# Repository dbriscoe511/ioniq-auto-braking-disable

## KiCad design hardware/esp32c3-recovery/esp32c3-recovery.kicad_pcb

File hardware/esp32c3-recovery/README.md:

# ESP32-C3 add-on: Parking Safety auto-disable

KiCad 10 schematic and PCB for the add-on board that taps the console switch panel
(CON1 of PCB IP-678A, see [../../docs/electronics.md](../../docs/electronics.md))
and presses the Parking Safety button at startup based on CAN status.

PDF: [out/esp32c3-recovery.pdf](out/esp32c3-recovery.pdf)

## Files

| File | What |
|---|---|
| `esp32c3-recovery.kicad_pro` / `.kicad_sch` | KiCad project and the single sheet |
| `esp32c3_recovery.kicad_sym` + `sym-lib-table` | Project symbol library (empty: every symbol is stock KiCad) |
| `tools/gen.py` | Generates the sheet and project library; **edit this, not the sheet** |
| `tools/check.sh` | Regenerate, ERC, netlist check against intended nets, library check, PDF/SVG/PNG export |
| `esp32c3-recovery.kicad_pcb` | The routed board (generated; **edit `tools/gen_pcb.py`**) |
| `esp32c3_recovery.pretty/` + `fp-lib-table` | Project footprints from `tools/footprints.py`: WROOM-02 (stock minus its 0.2 mm vias), WAGO 2060, TS-1187A switch |
| `esp32c3_recovery.3dshapes/` | 3D models for the WAGO, the switch and F1 (sources below) |
| `tools/gen_pcb.py` | Placement (`PLACE`), keep-outs, ground pours, stitching vias, JLC BOM/CPL |
| `tools/pcb.sh` | Full PCB build: schematic checks, place, Freerouting, pours, DRC, JLC outputs |
| `out/jlc/` | Upload set: `*-gerbers.zip`, `*-bom.csv`, `*-cpl.csv` |

Everything else uses stock KiCad symbols and footprints. Each JLC-assembled
part carries `Footprint` and `LCSC` fields.

## PCB

Sized for a **Hammond 1551K** box (1551KBK black, 1551KTBU translucent blue;
80 x 40 x 20 mm ABS). The outline is Hammond's maximum board size (74 x 34 mm,
with 6.25 mm notches at the top-right and bottom-left corners for the lid-screw
posts), shrunk by 0.25 mm on every side: 73.5 x 33.5 mm. Corners are rounded
R1, and the two inside notch corners R3 (Hammond's radius). 2 layers, 1.6 mm,
every part JLC-placed on the top side (Economic PCBA), including the ESP32-C3
module: nothing to hand-solder. DRC is clean (0 violations, 0 unconnected,
schematic parity OK).

- **Mounting: four 2.5 mm non-plated holes on a 40 x 28.5 mm rectangle.**
  - **H1 (top left) and H2 (bottom right) sit on the box's two PCB bosses.**
    Hammond puts them 17 mm from the left edge and 2.75 mm from the top of
    its maximum board, which is board (16.75, 2.5) here. Use Hammond's
    #2 x 3/16" self-tapping PCB screws (1551ATS100).
  - **H3 (top right) and H4 (bottom left)** complete the rectangle for bench
    standoffs; nothing sits under them in the box. 2.5 mm is tight for M2.5,
    so use M2 screws or standoffs there.
  - No top-layer tracks or vias within 2.7 mm of H1/H2, so the box screws'
    heads sit only on the ground pour. The board sits
  4 mm off the floor and the tallest part (the WAGOs, 4.5 mm) clears the lid by
  about 5.9 mm.
- **U2 is an ESP32-C3-WROOM-02-N4** (C2934560, 18 x 20 mm, 4 MB flash, PCB
  antenna, -40 to 85 C), placed by JLC. It lies on its side with the antenna
  end at the left edge, so Espressif's keep-out (5 mm round the antenna, in
  KiCad's footprint) covers the left 6.3 mm of the board and runs off the
  edge. Pins 10-18 (IO10..IO0) run along the top, 1-9 (3V3, EN, IO4..IO9,
  GND) along the bottom.
  - The project footprint is KiCad's stock one without its twelve 0.2 mm
    vias in the ground pad (JLC's standard minimum drill is 0.3 mm); five
    0.3 mm vias take their place.
  - No top-layer tracks under the module inside its pad rows.
  - The nearest screw to the antenna is H1's, about 10 mm from the antenna
    end.
- **3.3 V:** U4 AMS1117-3.3 from +5V (about 0.1 W), C7 22u at its output and
  C8 100n at the module's 3V3 pin. The L78M05 still makes 5V_REG for the
  TJA1051.
- **Reset, boot, strapping:** R8 10k + C9 1u on EN (power-on delay), SW2
  RESET and SW1 BOOT (TS-1187A, JLC basic), and 10k pull-ups on GPIO9, GPIO8
  and GPIO2. For the ROM bootloader, hold BOOT and tap RESET.
- **USB and debug pads:** J6 USB-C (HRO TYPE-C-31-M-12, C165948) with 5.1k
  CC pull-downs R12/R13, fitted by JLC, on the module's native USB
  (GPIO18/19). The cable plugs in from the board's bottom edge, which faces a
  long wall in the box. Next to it are bare test pads:
  - TP1 5V (VBUS), TP2 D-, TP3 D+, TP4 GND: the same native USB, for a
    pogo-pin or tack-soldered cable;
  - TP5 TX, TP6 RX: UART0, where the firmware logs.
  - VBUS reaches +5V through D4, so USB alone runs the board (the TJA1051
    stays off the bus without 12 V). The labels are on the bottom silkscreen.
- **J1-J5 are WAGO 2060-451/998-404 push-in terminals**, one per wire, wire
  entry facing the right end wall. From the top: VBAT, CANH, CANL, BTN, GND,
  printed at each entry on the top and under each terminal on the bottom.
  - The entry faces sit about 7.5 mm in from the board edge, about 8.3 mm
    from the box's inner wall. J1 and J5 are 8 mm either side of centre, so
    wires from one central hole can't enter them straight on. Either thread
    the harness through the end-wall hole, wire the board outside the box,
    then lower it in, or cut a U-slot down from the rim of the right end wall.
    The hole centre should be about 9.5 mm above the outside bottom (a guess
    from the 3D model). Thin wire (22-24 AWG) makes the fan-out easier.
  - GND is the terminal next to H2's screw.
  - Wire: 0.2-0.75 mm2 (24-18 AWG) solid, or stranded with the release button
    pressed, stripped 7-9 mm. Ferrules only for 0.25-0.34 mm2. Don't tin
    stranded wire.
  - The footprint follows WAGO's land pattern (data sheet 11.02.2026): 14 mm
    overall, a 6 mm pad under the conductor entry, a 3.5 mm pad at the back,
    and 2.0 mm wide (the 1.2 mm contact tail plus 0.4 mm each side).
  - Each terminal is held by its two solder pads only. Tie the harness down
    to the box (a cable tie through the grommet), and optionally put a bead of
    RTV across the five bodies after wiring.
- **D3, user LED:** red 0603 LED on GPIO1 (active high, ~1.3 mA through R7
  1k), at the top-left corner, board (8.0, 1.9) from the top-left corner. The
  box is opaque, so drill a ~2 mm hole in the lid above it. The translucent
  1551KTBU may also work, but blue plastic dims red light.
- **Regulator heat:** the DPAK tab connects solid to the top ground pour, with
  9 vias in the tab plus a ring beside it into the bottom pour.
- **Rules:** power nets (VBAT, 5V_REG, +5V, +3V3) use 0.5 mm tracks, other nets
  0.25 mm. GND is routed at 0.25 mm too; the pours on both layers carry
  its current. Clearance is 0.2 mm, vias 0.6/0.3 mm, copper-to-edge 0.3 mm or more.

**3D models** (`esp32c3_recovery.3dshapes/`, used unmodified; the footprints set the offset and rotation):
- `WAGO_2060-451_998-404.step`: the EasyEDA/LCSC model for C2765054, fetched
  with `easyeda2kicad --3d --lcsc_id=C2765054`.
- `Fuse_1812_4532Metric.step`: the EasyEDA/LCSC model for C70113 (F1), fetched
  the same way. KiCad ships none for that footprint; `MODEL_OVERRIDE` in
  `tools/gen_pcb.py` swaps it in.
- `SW_TS-1187A.step`: the EasyEDA/LCSC model for C318884 (SW1, SW2), with
  its footprint pads taken from JLC's footprint.
- All other parts, including the WROOM-02, use KiCad's stock models.

**Rebuild:** `JAVA=<java 25+> FREEROUTING=<freerouting-2.x.jar> tools/pcb.sh`.
`pcb.sh` re-runs Freerouting while its result changes. If a change leaves
unconnected pads, adjust `PLACE`; check two-terminal parts' pad 1 orientation
first.

### Before ordering

- **Check the fit against a real 1551K** if one is on hand: the hole positions
  and the corner notches come from Hammond's drawing (REV 31.08.2023), not a
  measured box.
- **Tick "Confirm Parts Placement" when ordering**, and check every part in
  JLC's placement preview: the polarity of U3 (pin 1), Q1, U1, D1, D2, D3 and
  D4, and the WAGO orientation, with the wire entry (6 mm pad) facing the
  right edge.
  - **New since the last preview check:** U2 (the module: antenna end at the
    left edge, pin 1 bottom-left), U4 (SOT-223, tab toward the top edge) and
    SW1/SW2. JLCKicadTools has no entry for the WROOM-02; the CPL uses
    KiCad's rotation, so correct it in the preview if JLC's model is turned.
  - The CPL adds SOIC +270, SOT-23 +180 and SOT-223 +180. The SOT-23 value
    comes from JLC's own preview on 2026-11-17, which showed Q1 90 degrees off
    with the JLCKicadTools -90. That preview also showed U1, D1, D2, D3, F1,
    U3 and the WAGOs correct.
- **WAGO position:** JLC's own footprint for C2765054 has its origin 0.57 mm
  toward the back pad from ours. The CPL reports that point, so JLC's part
  lands centred on our pads. If the preview still shows the terminals shifted
  along their length, correct it there.
- **Economic assembly:** JLC's part pages list "Economic and Standard" for
  the module C2934560, the WAGO C2765054, F1 C70113, U3 C38695, U4 C6186
  and D1 C19077573 (checked 2026-11-17). Order five WAGOs per board.
- Gerbers, drill files and the CPL share the bounding box's lower-left corner
  as origin.

## BOM (JLCPCB assembly)

Every part is placed by JLC (J6's shell pegs are through-hole, soldered in the
same pass); the test pads are bare copper. Part status was checked
against JLC's parts API on 2026-11-16/17.
Basic and preferred parts carry no feeder fee on Economic PCBA. Each plain
extended part type adds about $3 per order.

| Ref | Part | Package | LCSC | JLC status |
|---|---|---|---|---|
| R1, R7 | 1k | 0603 | C21190 | basic |
| R2, R8, R9, R10, R11 | 10k | 0603 | C25804 | basic |
| R3 | 200 | 0805 | C17540 | basic |
| R4 | 100k | 0603 | C25803 | basic |
| R5 | 27k | 0603 | C22967 | basic |
| R6 | 4.7k | 0603 | C23162 | basic |
| C1 | 1u 50V X7R | 0805 | C28323 | basic |
| C2, C4, C5, C6, C8 | 100n 50V X7R | 0603 | C14663 | basic |
| C3, C7 | 22u 25V X5R | 0805 | C45783 | basic |
| C9 | 1u 50V X5R | 0603 | C15849 | basic |
| U4 | AMS1117-3.3 | SOT-223 | C6186 | basic |
| SW1, SW2 | TS-1187A-B-A-B tactile switch | 5.1 x 5.1 mm SMD | C318884 | basic |
| U1 | L78M05ABDT-TR | DPAK | C58069 | basic |
| D2, D4 | B5819W | SOD-123 | C8598 | basic |
| Q1 | MMBT3904 | SOT-23 | C20526 | basic |
| D1 | SMBJ18A | SMB | C19077573 | preferred (no basic TVS exists) |
| U3 | TJA1051T/3/1J | SOIC-8 | C38695 | extended (no basic CAN transceiver exists) |
| F1 | mSMD050-60V | 1812 | C70113 | extended (no basic or preferred PTC exists) |
| J1-J5 | WAGO 2060-451/998-404 (x5) | SMD terminal | C2765054 | extended (one part type, one fee) |
| D3 | KT-0603R red LED | 0603 | C2286 | basic |
| U2 | ESP32-C3-WROOM-02-N4 | 18 x 20 mm module | C2934560 | extended |
| J6 | USB-C, HRO TYPE-C-31-M-12 | SMD + THT shell | C165948 | extended |
| R12, R13 | 5.1k | 0603 | C23186 | basic |

Five extended part types (U2, U3, F1, J1-J5, J6): about $15 in feeder fees per
order.

**CAN transceiver.** JLC has no basic CAN transceiver. Two are preferred
(fee-free). TJA1050T (C6952) needs 5 V, outputs 5 V on RXD and has no silent
pin, so it doesn't fit. SN65HVD230DR (C12084) runs on 3.3 V, and its RS-high
standby mode is a true listen-only mode (driver off, receiver unchanged), so it
would work with the same firmware. It is not used here because its bus pins
are rated only -4 to +16 V absolute maximum and it is rated to 85 C. The
TJA1051T/3 is the chip on the Adafruit CAN Pal. It is AEC-Q100, with -58 to
+58 V bus pins and the same S (silent) pin, for about $0.55 plus one
extended-part fee.

## Pin map (ESP32-C3-WROOM-02)

| GPIO | Use |
|---|---|
| GPIO3 (ADC) | Press sense: BTN through 100k/27k divider, ~1 V threshold |
| GPIO5 | TJA1051 S (silent). R6 4.7k pull-up keeps the transceiver silent; firmware drives it high by default |
| GPIO6 | TJA1051 TXD (transmit possible, but off by default) |
| GPIO7 | TJA1051 RXD |
| GPIO10 | Button press drive on CON1-5 (1k to MMBT3904 base, 10k base pull-down) |
| GPIO1 | D3 user LED (active high, R7 1k) |
| GPIO2/8/9 | Strapping pins: 10k pull-ups; SW1 BOOT pulls GPIO9 low |
| GPIO18/19 | Native USB D-/D+ (J6, TP2/TP3) |
| GPIO20/21 | UART0 RX/TX (TP6/TP5), firmware log |
| EN | 10k/1u reset delay, SW2 RESET |

## Assumptions to verify before building

- **BTN line = CON1 pin 5.** The Parking Safety switch is hardwired there
  (~200 ohms in series, other side to ground; not read by the panel MCU) and
  pin 5 idles at 12.2 V in the car. See docs/findings.md. Measured in the car
  with the firmware running: GPIO3 reads ~2.5 V released (BTN ~11.8 V) and
  ~0.1 V with Q1 on (BTN ~0.5 V), so R3 = 200 ohms (mirroring the factory switch
  path) carries at most ~2.4 mA.
- **R3 is now 0805 (125 mW), down from 1 W.** Against the panel's weak (~5k)
  pull-up it dissipates about 1 mW. The 1 W rating only covered a stiff 12 V
  source on BTN (0.7 W), which the in-car readings rule out. There is no basic
  1206 at 200 ohms (C18002, 0.25 W, is extended).
- **Regulator:** L78M05 in DPAK (35 V max in, above the SMBJ18A's 29.2 V
  clamp). It has no reverse-battery protection, but the tap is behind the
  panel's D1/D2. At 14.4 V in and ~80 mA average (more in Wi-Fi bursts) it
  dissipates ~0.75 W, so give the DPAK tab a copper pour of a few cm^2.
- **Transceiver supply:** TJA1051 VCC (4.5-5.5 V) is fed from `5V_REG`
  before D2, because the Schottky drop on `+5V` can fall below 4.5 V. On USB
  power alone the transceiver sees VCC under-voltage and disengages from the
  bus (zero load), so there is no CAN receive on the bench without 12 V.
  VIO is the board's 3.3 V (U4), so RXD is 3.3 V logic.
- **No CAN termination** on this board: the tap sits mid-bus.
- **Parts added after the design review:** F1 PTC fuse, which limits fault
  current if the TVS fails short. D2 Schottky, which stops USB 5 V from
  back-feeding the regulator; D4 does the same the other way, so the 12 V
  supply can't push current into a USB host.

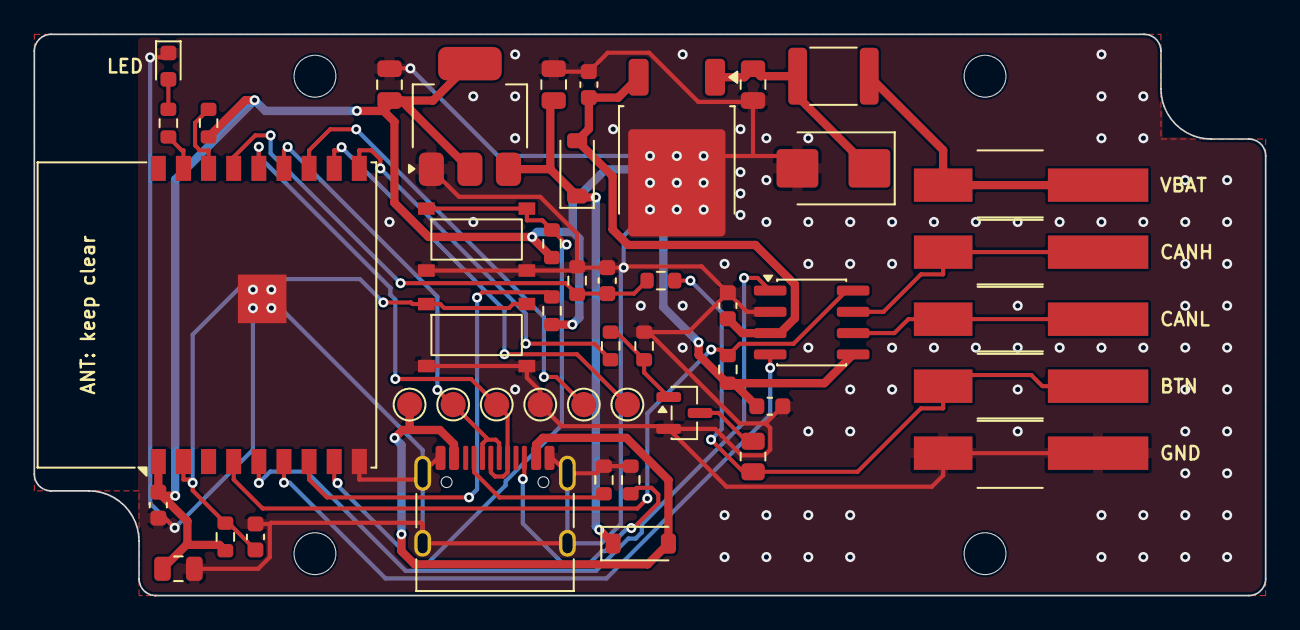
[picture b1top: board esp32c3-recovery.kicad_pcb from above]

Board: 2 copper layers, 73.5 x 33.5 mm, 51 parts (0 on the bottom side), 29 nets.

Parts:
C1: 1u 50V; C_0805_2012Metric
C2, C4, C5, C6, C8: 100n; C_0603_1608Metric
C3, C7, C10: 22u 25V; C_0805_2012Metric
C9: 1u; C_0603_1608Metric
D1: SMBJ18A; D_SMB
D2, D4: B5819W; D_SOD-123
D3: red; LED_0603_1608Metric
F1: 500mA 60V; Fuse_1812_4532Metric
H1, H2, H3, H4: #2; MountingHole_2.5mm
J1: VBAT; WAGO_2060-451_998-404
J2: CANH; WAGO_2060-451_998-404
J3: CANL; WAGO_2060-451_998-404
J4: BTN; WAGO_2060-451_998-404
J5: GND; WAGO_2060-451_998-404
J6: USB-C; USB_C_Receptacle_HRO_TYPE-C-31-M-12
Q1: MMBT3904; SOT-23
R1, R7: 1k; R_0603_1608Metric
R2, R8, R9, R10, R11: 10k; R_0603_1608Metric
R3: 200; R_0805_2012Metric
R4: 100k; R_0603_1608Metric
R5: 27k; R_0603_1608Metric
R6: 4.7k; R_0603_1608Metric
R12, R13: 5.1k; R_0603_1608Metric
SW1: BOOT; SW_TS-1187A
SW2: RESET; SW_TS-1187A
TP1: VBUS; TestPoint_Pad_D1.5mm
TP2: USB_DN; TestPoint_Pad_D1.5mm
TP3: USB_DP; TestPoint_Pad_D1.5mm
TP4: GND; TestPoint_Pad_D1.5mm
TP5: U0TXD; TestPoint_Pad_D1.5mm
TP6: U0RXD; TestPoint_Pad_D1.5mm
U1: L78M05; TO-252-2
U2: ESP32-C3-WROOM-02-N4; ESP32-C3-WROOM-02_JLC
U3: TJA1051T/3; SOIC-8_3.9x4.9mm_P1.27mm
U4: AMS1117-3.3; SOT-223-3_TabPin2

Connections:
+3V3: C6.1, C7.1, C8.1, C10.1, R6.1, R8.1, R9.1, R10.1, R11.1, U2.1, U3.5, U4.2
+5V: C3.1, D2.1, D4.1, U4.3
/5V_REG: C2.1, C5.1, D2.2, U1.3, U3.3
/BTN: J4.1, R3.1, R4.1
/BTN_DRIVE: R1.1, U2.10
/BTN_SENSE: C4.1, R4.2, R5.1, U2.15
/CANH: J2.1, U3.7
/CANL: J3.1, U3.6
/CAN_RX: U2.6, U3.4
/CAN_S: R6.2, U2.4, U3.8
/CAN_TX: U2.5, U3.1
/CC1: J6.A5, R12.1
/CC2: J6.B5, R13.1
/EN: C9.1, R8.2, SW2.1, U2.2
/IO2_STRAP: R11.2, U2.16
/IO8_STRAP: R10.2, U2.7
/IO9_BOOT: R9.2, SW1.1, U2.8
/LED: R7.1, U2.17
/U0RXD: TP6.1, U2.11
/U0TXD: TP5.1, U2.12
/USB_DN: J6.A7, J6.B7, TP2.1, U2.13
/USB_DP: J6.A6, J6.B6, TP3.1, U2.14
/VBAT_F: C1.1, D1.1, F1.2, U1.1
/VBUS: D4.2, J6.A4, J6.A9, J6.B4, J6.B9, TP1.1
GND: C1.2, C2.2, C3.2, C4.2, C5.2, C6.2, C7.2, C8.2, C9.2, C10.2, D1.2, D3.1, J5.1, J6.A1, J6.A12, J6.B1, J6.B12, J6.SH, Q1.2, R2.2, R5.2, R12.2, R13.2, SW1.2, SW2.2, TP4.1, U1.2, U2.9, U2.19, U3.2, U4.1
unnamed: D3.2, R7.2
unnamed: F1.1, J1.1
unnamed: Q1.1, R1.2, R2.1
unnamed: Q1.3, R3.2

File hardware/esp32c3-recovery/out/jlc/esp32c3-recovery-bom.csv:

Comment,Designator,Footprint,LCSC Part #
1u 50V,C1,C_0805_2012Metric,C28323
100n,"C2,C4,C5,C6,C8",C_0603_1608Metric,C14663
22u 25V,"C3,C7,C10",C_0805_2012Metric,C45783
1u,C9,C_0603_1608Metric,C15849
SMBJ18A,D1,D_SMB,C19077573
B5819W,"D2,D4",D_SOD-123,C8598
red,D3,LED_0603_1608Metric,C2286
500mA 60V,F1,Fuse_1812_4532Metric,C70113
WAGO 2060-451,"J1,J2,J3,J4,J5",WAGO_2060-451_998-404,C2765054
USB-C,J6,USB_C_Receptacle_HRO_TYPE-C-31-M-12,C165948
MMBT3904,Q1,SOT-23,C20526
1k,"R1,R7",R_0603_1608Metric,C21190
5.1k,"R12,R13",R_0603_1608Metric,C23186
10k,"R2,R8,R9,R10,R11",R_0603_1608Metric,C25804
200,R3,R_0805_2012Metric,C17540
100k,R4,R_0603_1608Metric,C25803
27k,R5,R_0603_1608Metric,C22967
4.7k,R6,R_0603_1608Metric,C23162
SW TS-1187A,"SW1,SW2",SW_TS-1187A,C318884
L78M05,U1,TO-252-2,C58069
ESP32-C3-WROOM-02-N4,U2,ESP32-C3-WROOM-02_JLC,C2934560
TJA1051T/3,U3,SOIC-8_3.9x4.9mm_P1.27mm,C38695
AMS1117-3.3,U4,SOT-223-3_TabPin2,C6186

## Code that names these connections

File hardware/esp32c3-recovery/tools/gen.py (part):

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    for i, t in enumerate(["CON1-1  VBAT", "CON1-8  CAN-H", "CON1-7  CAN-L",
                           "CON1-5  BTN", "CON1-16  GND"]):
        s.text(t, 34.29, VB_Y + 2.54 * i + 0.635, justify="right bottom")
    for pin, name in (("2", "CANH"), ("3", "CANL"), ("4", "BTN")):
        p = J[pin]
        s.wire(p, (p[0] + 7.62, p[1]))
        s.label(name, (p[0] + 7.62, p[1]))
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    s.wire(U1["3"], (C2["1"][0], VB_Y), C2["1"])
    s.wire((C2["1"][0], VB_Y), D2["2"])
    s.power("power:PWR_FLAG", 88.9, VB_Y)
    s.label("VBAT_F", (99.06, VB_Y))
    s.label("5V_REG", (C2["1"][0], VB_Y))
    j5 = J["5"]
    s.wire(j5, (j5[0] + 2.54, j5[1]), (j5[0] + 2.54, GND_Y), (C3["2"][0], GND_Y))
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    s.power("power:GND", *U2["9"])
    for num in ("18", "3"):          # IO0, IO4
        s.no_connect(f"U2.{num}")
    for pin, name in (("2", "EN"), ("17", "LED"), ("16", "IO2_STRAP"), ("15", "BTN_SENSE"),
                      ("4", "CAN_S"), ("5", "CAN_TX"), ("6", "CAN_RX"), ("7", "IO8_STRAP"),
                      ("8", "IO9_BOOT"), ("10", "BTN_DRIVE"), ("13", "USB_DN"), ("14", "USB_DP")):
        p = U2[pin]
        s.wire(p, (p[0] - 12.7, p[1]))
        s.label(name, (p[0] - 12.7, p[1]))
    for pin, name in (("11", "U0RXD"), ("12", "U0TXD")):
        p = U2[pin]
        s.wire(p, (p[0] + 2.54, p[1]))
        s.label(name, (p[0] + 2.54, p[1]))
    s.block("MCU (module JLC-placed)", 168.91, 30.48, 226.06, 102.87)

    # ---------------- Press sense (BTN -> GPIO3) --------------------------
    SY = 106.68
    R4 = s.place_by_pin("Device:R", "R4", "100k", "1", (130.81, SY), rot=90,
                        ref_at=(0, -2.54), val_at=(0, 2.54), fields=jlc("C25803", R0603))
    s.wire((123.19, SY), R4["1"])
    s.label("BTN", (123.19, SY), justify="right bottom")
    nx = 144.78
    R5 = s.place_by_pin("Device:R", "R5", "27k", "1", (nx, SY + 5.08),
                        ref_at=(2.54, -1.27), val_at=(2.54, 1.27), just="left",
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    s.wire(R5["2"], (nx, g), (C4["2"][0], g), C4["2"])
    s.power("power:GND", nx + 5.08, g)
    s.wire((C4["1"][0], SY), (C4["1"][0] + 7.62, SY))
    s.label("BTN_SENSE", (C4["1"][0] + 7.62, SY), justify="right bottom")
    s.block("PRESS SENSE (ADC, ~1 V threshold)", 110.49, 97.79, 166.37, 133.35)

    # ---------------- CAN -------------------------------------------------
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                 fields=jlc("C38695", "Package_SO:SOIC-8_3.9x4.9mm_P1.27mm",
                            "TJA1051T/3/1J CAN transceiver (same chip as the Adafruit CAN Pal). "
                            "VCC 5 V, VIO 3.3 V logic. S high = silent (transmitter off). JLC extended."))
    for pin, name in (("1", "CAN_TX"), ("4", "CAN_RX"), ("8", "CAN_S")):
        p = U3[pin]
        s.wire(p, (p[0] - 10.16, p[1]))
        s.label(name, (p[0] - 10.16, p[1]))
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    s.label("5V_REG", (vcc[0] - 7.62, top[1]))
    s.power("power:GND", *C5["2"])
    s.power("power:GND", *U3["2"])
    for pin, name in (("7", "CANH"), ("6", "CANL")):
        p = U3[pin]
        s.wire(p, (p[0] + 7.62, p[1]))
        s.label(name, (p[0] + 7.62, p[1]))
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                                   "S pull-up: transceiver silent unless firmware drives GPIO5 low"))
    s.power("power:+3V3", *R6["1"])
    s.wire(R6["2"], (R6["2"][0], R6["2"][1] + 2.54), (R6["2"][0] + 8.89, R6["2"][1] + 2.54))
    s.label("CAN_S", (R6["2"][0] + 8.89, R6["2"][1] + 2.54), justify="right bottom")
    C6 = s.place_by_pin("Device:C", "C6", "100n", "1", (271.78, ry),
                        ref_at=(2.54, -1.27), val_at=(2.54, 1.27), just="left",
                        fields=jlc("C14663", C0603, "VIO decoupling"))
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    s.power("power:GND", *C6["2"])
    s.block("CAN (silent by default)", 227.33, 30.48, 284.48, 82.55)

    # ---------------- Button press output (GPIO10 -> NPN -> BTN) ----------
    BY = 111.76
    R1 = s.place_by_pin("Device:R", "R1", "1k", "1", (233.68, BY), rot=90,
                        ref_at=(0, -2.54), val_at=(0, 2.54), fields=jlc("C21190", R0603))
    s.wire((R1["1"][0] - 5.08, BY), R1["1"])
    s.label("BTN_DRIVE", (R1["1"][0] - 5.08, BY))
    bx = 246.38
    Q1 = s.place_by_pin("Transistor_BJT:MMBT3904", "Q1", "MMBT3904", "1", (bx + 5.08, BY),
                        ref_at=(5.08, -1.27), val_at=(5.08, 1.27), just="left",
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    s.wire(R3["2"], Q1["3"])
    top = (R3["1"][0], R3["1"][1] - 2.54)
    s.wire(R3["1"], top, (top[0] + 12.7, top[1]))
    s.label("BTN", (top[0] + 12.7, top[1]))
    s.block("BUTTON PRESS OUTPUT", 227.33, 88.9, 284.48, 133.35)

    # ---------------- User LED (GPIO1, active high) -----------------------
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    s.power("power:GND", *SW2["2"])
    bt = pullup("R9", 342.9, "IO9_BOOT", "IO9 (BOOT strap) pull-up")
    s.wire((bt[0] - 7.62, bt[1]), bt)
    s.label("IO9_BOOT", (bt[0] - 7.62, bt[1]))
    SW1 = s.place_by_pin("Switch:SW_Push", "SW1", "BOOT", "1", (bt[0], bt[1] + 5.08), rot=270,
                         ref_at=(2.54, -1.27), val_at=(2.54, 1.27), just="left",
                         fields=jlc("C318884", "esp32c3_recovery:SW_TS-1187A",
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
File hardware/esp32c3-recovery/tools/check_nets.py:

#!/usr/bin/env python3
"""Compare the exported KiCad netlist against the intended connectivity.

ERC passes on a miswired divider, so this is the real wiring test.
"""
import sys

from sexp import find, findall, parse

EXPECTED = {
    "VBAT_IN (tap -> fuse)": {"J1.1", "F1.1"},
    "VBAT_F": {"F1.2", "D1.1", "C1.1", "U1.1"},
    "5V_REG": {"U1.3", "C2.1", "D2.2", "U3.3", "C5.1"},
    "+5V": {"D2.1", "C3.1", "U4.3", "D4.1"},
    "VBUS": {"D4.2", "J6.A4", "J6.A9", "J6.B4", "J6.B9", "TP1.1"},
    "+3V3": {"U4.2", "C7.1", "C8.1", "C10.1", "U2.1", "U3.5", "R6.1", "C6.1",
             "R8.1", "R9.1", "R10.1", "R11.1"},
    "EN": {"U2.2", "R8.2", "C9.1", "SW2.1"},
    "IO9_BOOT": {"U2.8", "R9.2", "SW1.1"},
    "IO8_STRAP": {"U2.7", "R10.2"},
    "IO2_STRAP": {"U2.16", "R11.2"},
    "USB_DN (GPIO18)": {"U2.13", "J6.A7", "J6.B7", "TP2.1"},
    "USB_DP (GPIO19)": {"U2.14", "J6.A6", "J6.B6", "TP3.1"},
    "CC1": {"J6.A5", "R12.1"},
    "CC2": {"J6.B5", "R13.1"},
    "U0TXD": {"U2.12", "TP5.1"},
    "U0RXD": {"U2.11", "TP6.1"},
    "CAN_S (GPIO5)": {"U2.4", "U3.8", "R6.2"},
    "CAN_TX (GPIO6)": {"U2.5", "U3.1"},
    "CAN_RX (GPIO7)": {"U2.6", "U3.4"},
    "GND": {"J5.1", "D1.2", "C1.2", "U1.2", "C2.2", "C3.2", "U2.9", "U2.19", "R5.2", "C4.2",
            "U3.2", "C5.2", "C6.2", "R2.2", "Q1.2", "D3.1", "U4.1", "C7.2", "C8.2", "C9.2",
            "C10.2", "SW1.2", "SW2.2", "R12.2", "R13.2", "J6.A1", "J6.A12", "J6.B1", "J6.B12",
            "J6.SH", "TP4.1"},
    "CANH": {"J2.1", "U3.7"},
    "CANL": {"J3.1", "U3.6"},
    "BTN": {"J4.1", "R4.1", "R3.1"},
    "BTN_SENSE (GPIO3)": {"R4.2", "R5.1", "C4.1", "U2.15"},
    "BTN_DRIVE (GPIO10)": {"U2.10", "R1.1"},
    "Q1 base": {"R1.2", "R2.1", "Q1.1"},
    "Q1 collector": {"Q1.3", "R3.2"},
    "LED (GPIO1)": {"U2.17", "R7.1"},
    "LED anode": {"R7.2", "D3.2"},
}


def main(path):
    net = parse(open(path).read())
    got = {}
    for n in findall(find(net, "nets"), "net"):
        nodes = {f"{find(x, 'ref')[1]}.{find(x, 'pin')[1]}" for x in findall(n, "node")}
        nodes = {x for x in nodes if not x.startswith("#")}
        if nodes:
            got[str(find(n, "name")[1])] = nodes
    want = {frozenset(v): k for k, v in EXPECTED.items()}
    ok = True
    matched = set()
    for name, nodes in sorted(got.items()):
        key = frozenset(nodes)
        if key in want:
            matched.add(key)
        elif len(nodes) == 1:
            pass  # single unconnected pin (no-connect flagged), checked below
        else:
            ok = False
            print(f"UNEXPECTED net {name}: {sorted(nodes)}")
    for key, label in want.items():
        if key not in matched:
            ok = False
            print(f"MISSING net {label}: {sorted(key)}")
    singles = sorted(next(iter(v)) for v in got.values() if len(v) == 1)
    print("single-pin nets:", singles)
    print("NETLIST OK" if ok else "NETLIST MISMATCH")
    return 0 if ok else 1


if __name__ == "__main__":
    sys.exit(main(sys.argv[1]))
